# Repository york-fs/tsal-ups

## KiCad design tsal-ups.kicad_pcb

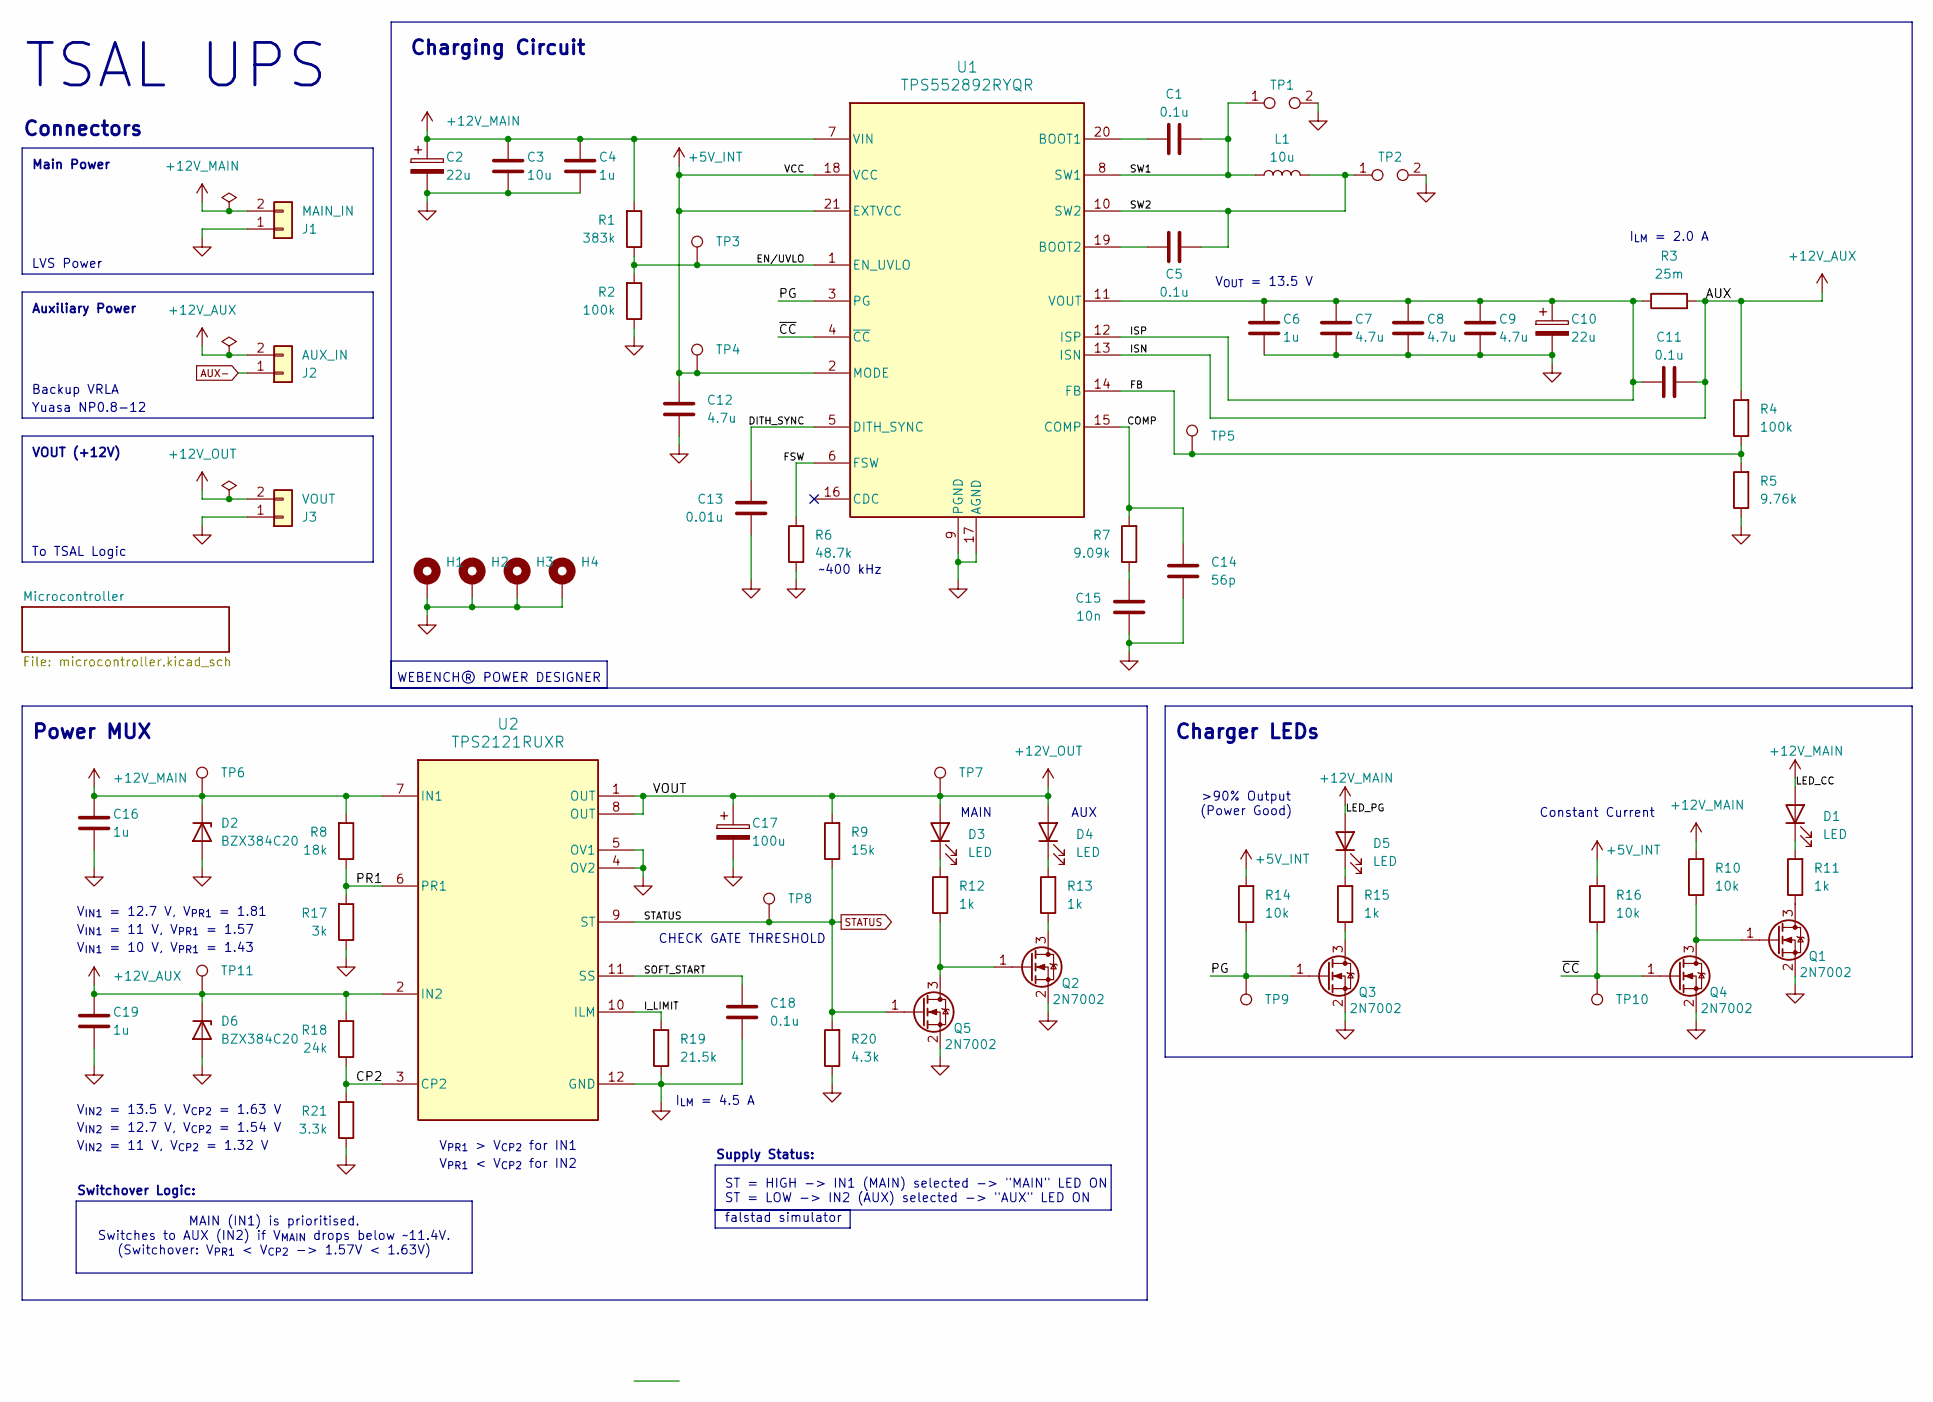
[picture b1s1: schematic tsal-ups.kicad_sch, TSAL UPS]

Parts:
C1, C5, C11, C18: 0.1u; C_0603_1608Metric
C2, C10: 22u; CP_Elec_6.3x7.7
C3: 10u; C_0805_2012Metric
C4, C6, C16, C19: 1u; C_0603_1608Metric
C7, C8, C9, C12: 4.7u; C_0805_2012Metric
C13: 0.01u; C_0603_1608Metric
C14: 56p; C_0603_1608Metric
C15: 10n; C_0603_1608Metric
C17: 100u; CP_Elec_6.3x7.7
D1, D3, D4, D5: LED; LED_0603_1608Metric
D2, D6: BZX384C20; D_SOD-323
H1, H2, H3, H4: MountingHole_Pad; MountingHole_3.2mm_M3_Pad_Via
J1: MAIN_IN; MolexMicrofitPlus1x2
J2: AUX_IN; MolexMicrofitPlus1x2
J3: VOUT; MolexMicrofitPlus1x2
L1: 10u; L_APV_APH0850
Q1, Q2, Q3, Q4, Q5: 2N7002; SOT-23
R1: 383k; R_0603_1608Metric
R2, R4: 100k; R_0603_1608Metric
R3: 25m; R_1206_3216Metric
R5: 9.76k; R_0603_1608Metric
R6: 48.7k; R_0603_1608Metric
R7: 9.09k; R_0603_1608Metric
R8: 18k; R_0603_1608Metric
R9: 15k; R_0603_1608Metric
R10, R14, R16: 10k; R_0603_1608Metric
R11, R12, R13, R15: 1k; R_0603_1608Metric
R17: 3k; R_0603_1608Metric
R18: 24k; R_0603_1608Metric
R19: 21.5k; R_0603_1608Metric
R20: 4.3k; R_0603_1608Metric
R21: 3.3k; R_0603_1608Metric
TP1, TP2: TestPoint_2Pole; TestPoint_2Pads_Pitch2.54mm_Drill1.0mm
TP3, TP4, TP5, TP6, TP7, TP8, TP9, TP10, TP11: TestPoint; TestPoint_Pad_D1.5mm
U1: TPS552892RYQR
U2: TPS2121RUXR; RUX0012A

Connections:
+5V_INT: C12.2, R14.2, R16.2, TP4.1, U1.2 (MODE), U1.18 (VCC), U1.21 (EXTVCC)
+12V_AUX: C11.1, C19.2, D6.1 (K), J2.2, R3.2, R4.2, R18.2, TP11.1, U1.13 (ISN), U2.2 (IN2)
+12V_MAIN: C2.1, C3.2, C4.2, C16.2, D1.2 (A), D2.1 (K), D5.2 (A), J1.2, R1.2, R8.2, R10.2, TP6.1, U1.7 (VIN), U2.7 (IN1)
+12V_OUT: C17.1, D3.2 (A), D4.2 (A), J3.2, R9.2, TP7.1, U2.1 (OUT), U2.8 (OUT); also elsewhere on the board
/COMP: C14.2, R7.2, U1.15 (COMP)
/CP2: R18.1, R21.2, U2.3 (CP2)
/DITH_SYNC: C13.2, U1.5 (DITH_SYNC)
/EN/UVLO: R1.1, R2.2, TP3.1, U1.1 (EN_UVLO)
/FB: R4.1, R5.2, TP5.1, U1.14 (FB)
/FSW: R6.2, U1.6 (FSW)
/ISP: C6.2, C7.2, C8.2, C9.2, C10.1, C11.2, R3.1, U1.11 (VOUT), U1.12 (ISP)
/I_LIMIT: R19.2, U2.10 (ILM)
/PG: Q3.1 (G), R14.1, TP9.1, U1.3 (PG)
/PR1: R8.1, R17.2, U2.6 (PR1)
/SOFT_START: C18.2, U2.11 (SS)
/SW1: C1.2, L1.1, TP1.1, U1.8 (SW1)
/SW2: C5.2, L1.2, TP2.1, U1.10 (SW2)
/~CC: Q4.1 (G), R16.1, TP10.1, U1.4 (~CC)
AUX-: J2.1; also elsewhere on the board
GND: C2.2, C3.1, C4.1, C6.1, C7.1, C8.1, C9.1, C10.2, C12.1, C13.1, C14.1, C15.1, C16.1, C17.2, C18.1, C19.1, D2.2 (A), D6.2 (A), H1.1, H2.1, H3.1, H4.1, J1.1, J3.1, Q1.2 (S), Q2.2 (S), Q3.2 (S), Q4.2 (S), Q5.2 (S), R2.1, R5.1, R6.1, R17.1, R19.1, R20.1, R21.1, TP1.2, TP2.2, U1.9 (PGND), U1.17 (AGND), U2.4 (OV2), U2.5 (OV1), U2.12 (GND); also elsewhere on the board
unnamed: C15.2, R7.1
unnamed: D1.1 (K), R11.2
unnamed: D3.1 (K), R12.2
unnamed: D4.1 (K), R13.2
unnamed: D5.1 (K), R15.2
unnamed: Q1.3 (D), R11.1
unnamed: Q1.1 (G), Q4.3 (D), R10.1
unnamed: Q2.3 (D), R13.1
unnamed: Q2.1 (G), Q5.3 (D), R12.1
unnamed: Q3.3 (D), R15.1
unnamed: C1.1, U1.20 (BOOT1)
unnamed: C5.1, U1.19 (BOOT2)
STATUS: Q5.1 (G), R9.1, R20.2, TP8.1, U2.9 (ST); also elsewhere on the board

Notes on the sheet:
falstad simulator
VOUT (+12V)
ST = HIGH -> IN1 (MAIN) selected -> "MAIN" LED ON ST = LOW -> IN2 (AUX) selected -> "AUX" LED ON
MAIN (IN1) is prioritised. Switches to AUX (IN2) if V_{MAIN} drops below ~11.4V. (Switchover: V_{PR1} < V_{CP2} -> 1.57V < 1.63V)
Charging Circuit
V_{IN1} = 11 V, V_{PR1} = 1.57
Supply Status:
WEBENCH® POWER DESIGNER
~400 kHz
V_{OUT} = 13.5 V
LVS Power
V_{IN2} = 11 V, V_{CP2} = 1.32 V
V_{IN1} = 10 V, V_{PR1} = 1.43
Charger LEDs
V_{IN2} = 12.7 V, V_{CP2} = 1.54 V
TSAL UPS
I_{LM} = 2.0 A
To TSAL Logic
V_{IN1} = 12.7 V, V_{PR1} = 1.81
MAIN
V_{PR1} < V_{CP2} for IN2
I_{LM} = 4.5 A
Backup VRLA
V_{PR1} > V_{CP2} for IN1
Constant Current
AUX
Power MUX
Auxiliary Power
Connectors
V_{IN2} = 13.5 V, V_{CP2} = 1.63 V
CHECK GATE THRESHOLD
>90% Output (Power Good)
Main Power
Yuasa NP0.8-12
Switchover Logic:

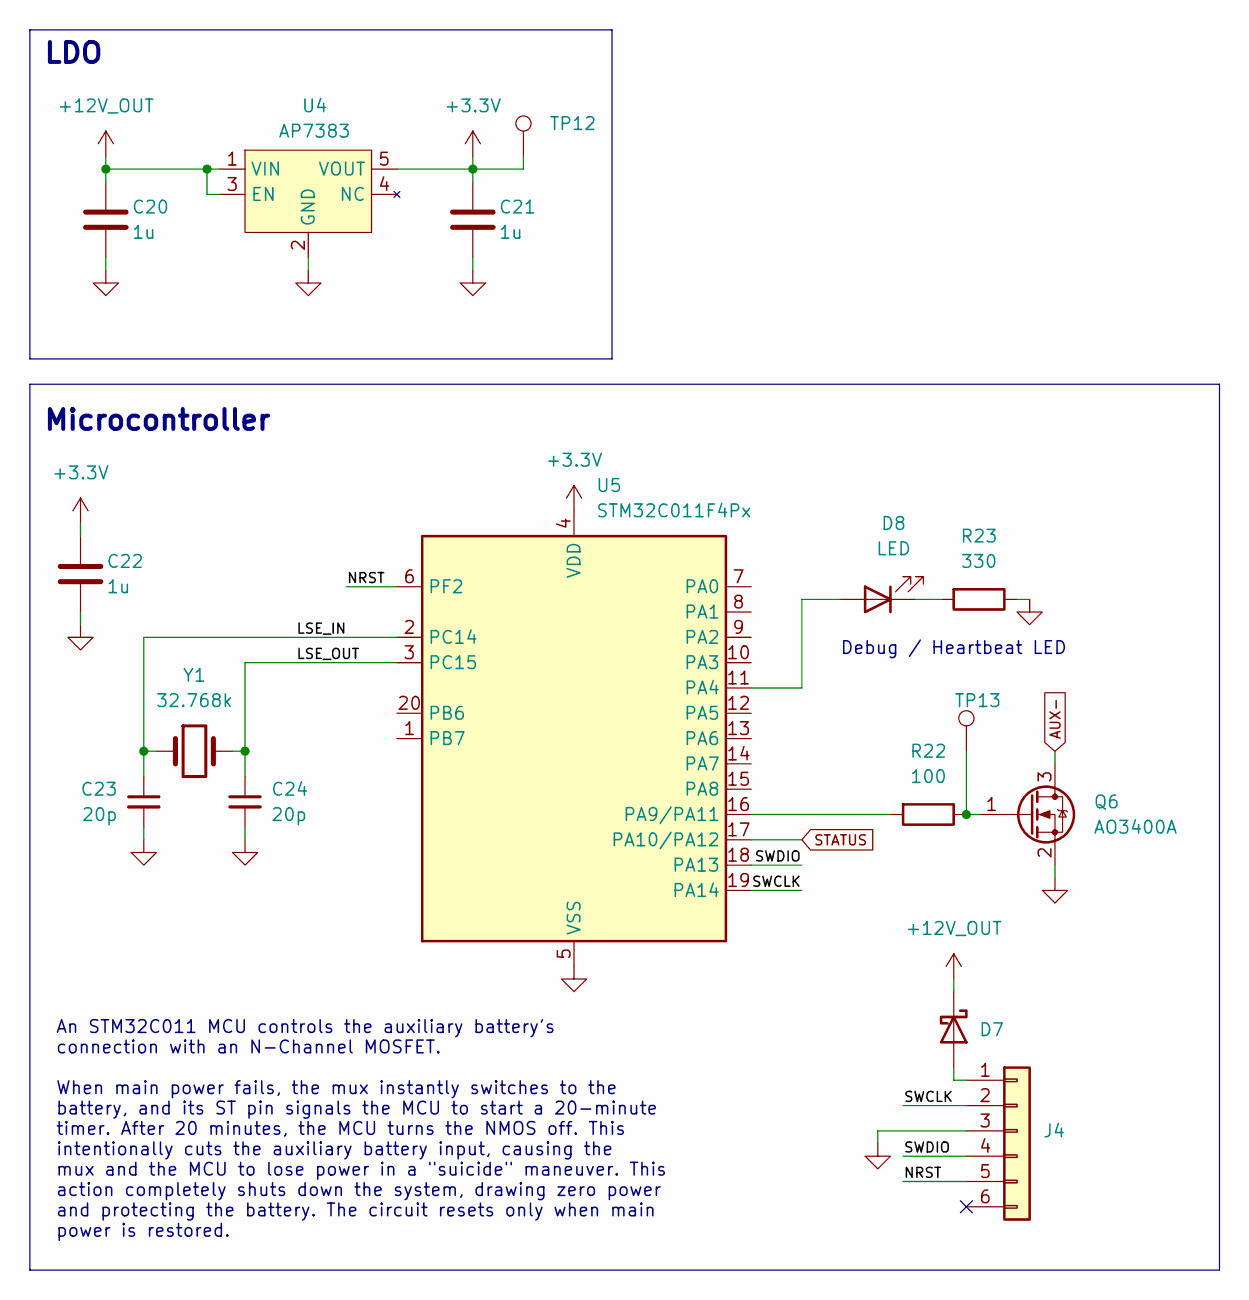
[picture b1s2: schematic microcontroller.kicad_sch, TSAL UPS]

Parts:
C20, C21, C22: 1u; C_0603_1608Metric
C23, C24: 20p; C_0603_1608Metric
D7: D_Schottky; D_SOD-323; Mfr # NSR0530H
D8: LED; LED_0603_1608Metric
J4: Conn_01x06; IDC-Connector-2x3
Q6: AO3400A; SOT-23
R22: 100; R_0603_1608Metric
R23: 330; R_0603_1608Metric
TP12, TP13: TestPoint; TestPoint_Pad_D1.5mm
U4: AP7383; TSOT-23-5
U5: STM32C011F4Px; TSSOP-20_4.4x6.5mm_P0.65mm
Y1: 32.768k; Crystal_SMD_G8-2Pin_3.2x1.5mm

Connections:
+3.3V: C21.2, C22.2, TP12.1, U4.5 (VOUT), U5.4 (VDD)
+12V_OUT: C20.2, D7.1 (K), U4.1 (VIN), U4.3 (EN); also elsewhere on the board
/Microcontroller/LSE_IN: C23.1, U5.2 (PC14), Y1.1
/Microcontroller/LSE_OUT: C24.1, U5.3 (PC15), Y1.2
/Microcontroller/NRST: J4.5, U5.6 (PF2)
/Microcontroller/SWCLK: J4.2, U5.19 (PA14)
/Microcontroller/SWDIO: J4.4, U5.18 (PA13)
AUX-: Q6.3 (D); also elsewhere on the board
GND: C20.1, C21.1, C22.1, C23.2, C24.2, J4.3, Q6.2 (S), R23.1, U4.2 (GND), U5.5 (VSS); also elsewhere on the board
unnamed: D7.2 (A), J4.1
unnamed: D8.2 (A), U5.11 (PA4)
unnamed: D8.1 (K), R23.2
unnamed: Q6.1 (G), R22.1, TP13.1
unnamed: R22.2, U5.16 (PA9/PA11)
STATUS: U5.17 (PA10/PA12); also elsewhere on the board

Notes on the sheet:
Debug / Heartbeat LED
LDO
An STM32C011 MCU controls the auxiliary battery's connection with an N-Channel MOSFET. When main power fails, the mux instantly switches to the battery, and its ST pin signals the MCU to start a 20-minute timer. After 20 minutes, the MCU turns the NMOS off. This intentionally cuts the auxiliary bat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
Microcontroller

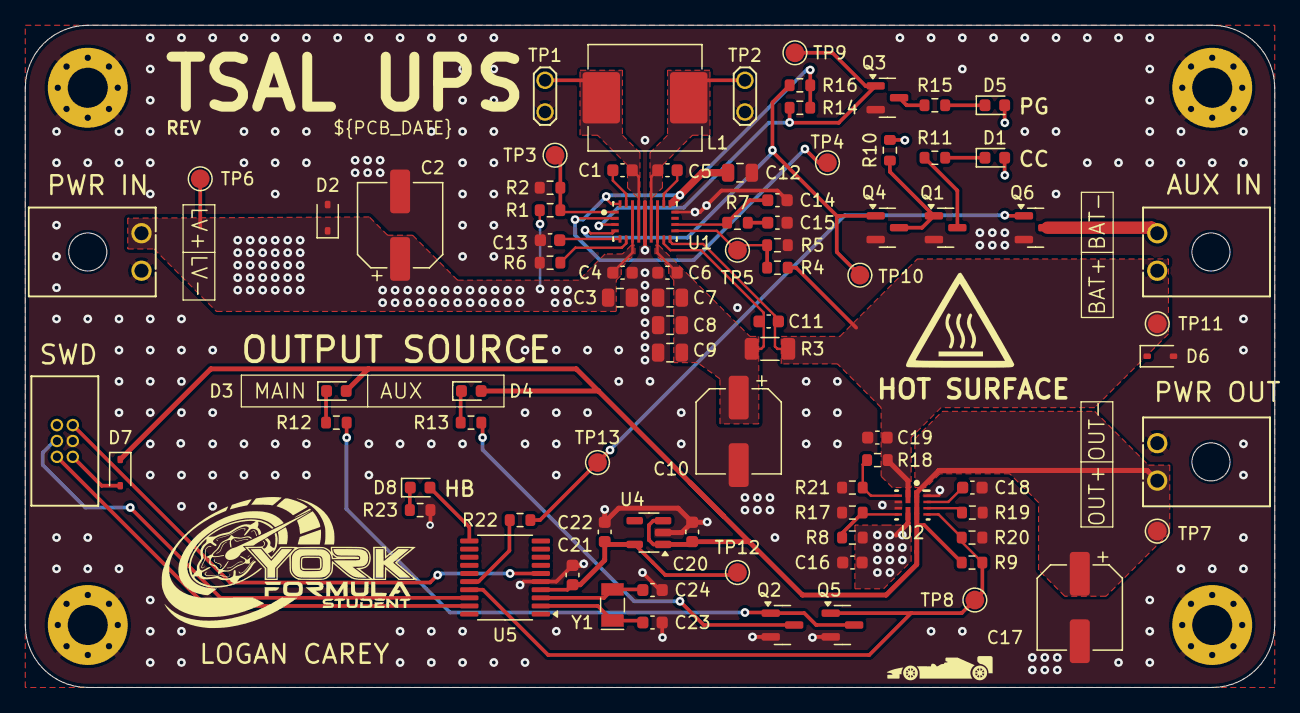
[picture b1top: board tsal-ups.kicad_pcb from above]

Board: 4 copper layers, 100.0 x 53.0 mm, 88 parts (0 on the bottom side), 44 nets.

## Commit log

2025-10-30 kicad-library: Update to latest version
2025-11-03 Revision A
2025-11-22 meta: Update gitignore
2025-11-22 meta: Set LF line endings explicitly
